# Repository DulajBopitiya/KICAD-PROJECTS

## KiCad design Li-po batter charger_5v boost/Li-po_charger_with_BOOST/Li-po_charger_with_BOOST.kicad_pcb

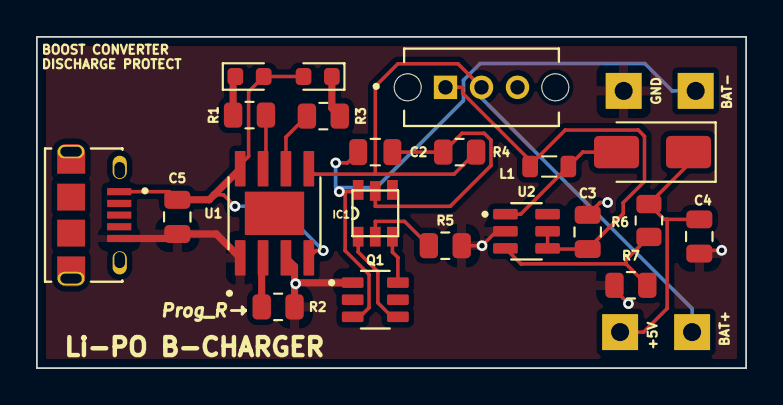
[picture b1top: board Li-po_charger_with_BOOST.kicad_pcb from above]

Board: 2 copper layers, 39.4 x 18.4 mm, 25 parts (0 on the bottom side), 17 nets.

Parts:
C2: 0.1u; C_0805_2012Metric
C3, C4: 22u; C_0805_2012Metric
C5: 10u; C_0805_2012Metric
D1: RED; LED_0603_1608Metric
D2: GREEN; LED_0603_1608Metric
D3: SS34; D_SMA
H1: BAT+; MountingHole_2.2mm_M2_Pad
H2: BAT-; MountingHole_2.2mm_M2_Pad
H4: GND; MountingHole_2.2mm_M2_Pad
H5: +5V; MountingHole_2.2mm_M2_Pad
IC1: FS312F-G; SOT23-6
J2: 10118194-0001LF; AMPHENOL_10118194-0001LF
L1: 22uH; L_0805_2012Metric
Q1: FS8205; SOT95P280X145-6N
R1, R3, R7: 1K; R_0805_2012Metric
R2, R5: 2K; R_0805_2012Metric
R4: 100; R_0805_2012Metric
R6: 7K5; R_0805_2012Metric
S1: OS102011MS2QN1; SW_OS102011MS2QN1
U1: TP4056; SOP127P600X175-9N
U2: MT3608; SOT95P280X145-6N

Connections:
/BAT: H1.1, R4.2, S1.2, U1.5 (BAT)
/BAT-: C2.1, H2.1, IC1.6 (GND), Q1.3
/VBUS: C5.1, D1.2 (A), D2.2 (A), J2.1, U1.4 (VCC), U1.8 (CE)
GND: C3.2, C4.2, C5.2, H4.1, J2.5, Q1.1, R2.2, R5.2, R7.1, U1.1 (TEMP), U1.3 (GND), U2.2 (GND)
unnamed: D1.1 (K), R1.2
unnamed: D2.1 (K), R3.1
unnamed: D3.2 (A), L1.2, U2.1 (SW)
unnamed: C4.1, D3.1 (K), H5.1, R6.2
unnamed: IC1.2 (CS), R5.1
unnamed: IC1.3 (OC), Q1.6
unnamed: IC1.1 (OD), Q1.4
unnamed: C2.2, IC1.5 (VCC), R4.1
unnamed: R2.1, U1.2 (PROG)
unnamed: R1.1, U1.7 (~CHRG)
unnamed: R3.2, U1.6 (~STDBY)
unnamed: C3.1, L1.1, S1.1, U2.4 (EN), U2.5 (IN)
unnamed: R6.1, R7.2, U2.3 (FB)

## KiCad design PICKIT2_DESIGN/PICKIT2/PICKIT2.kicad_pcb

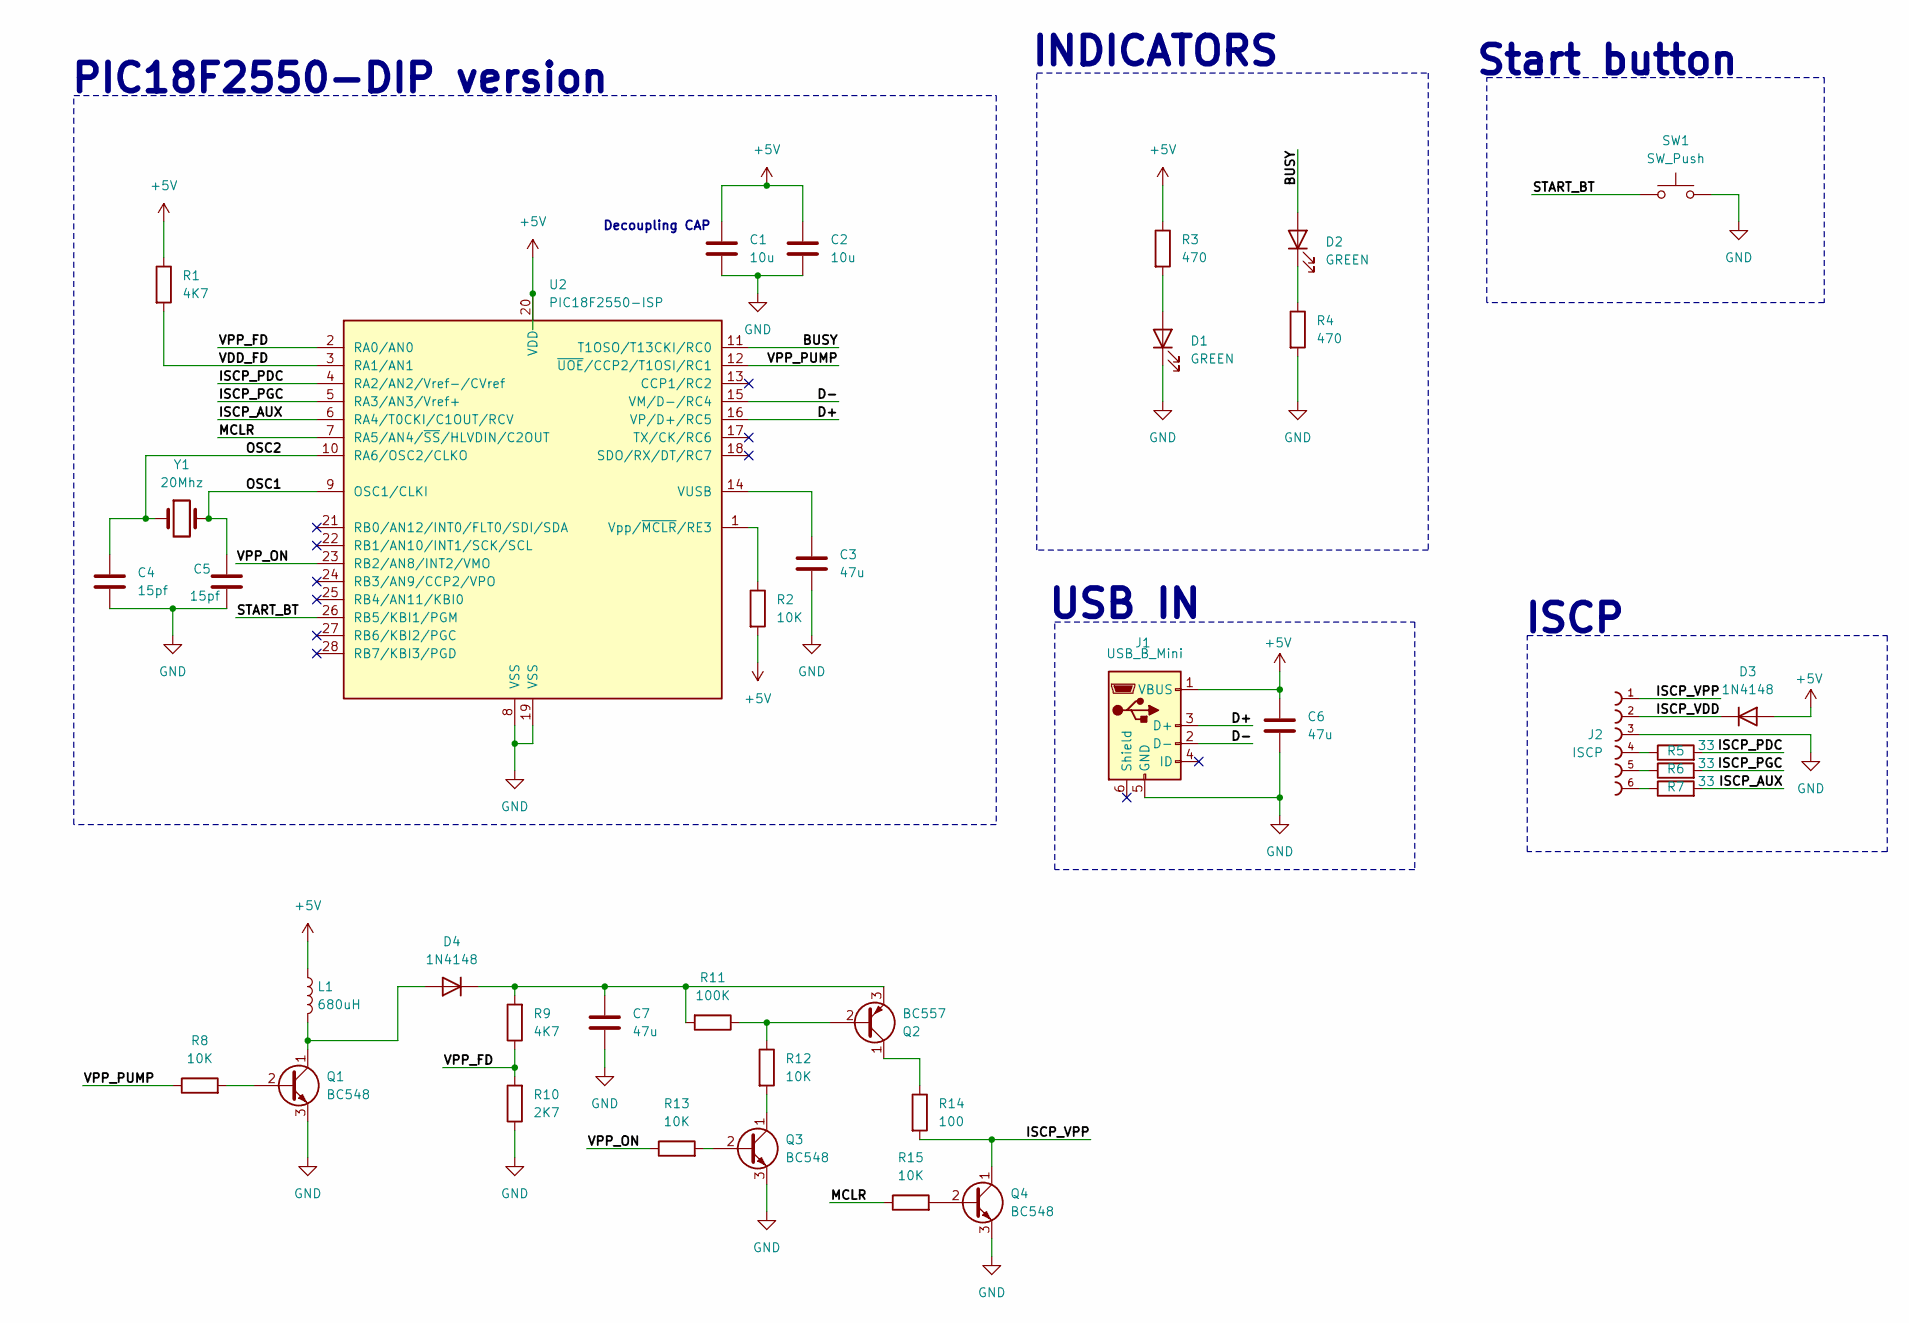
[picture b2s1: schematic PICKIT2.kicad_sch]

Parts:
C1, C2: 10u; C_0805_2012Metric
C3, C6, C7: 47u; C_0805_2012Metric
C4, C5: 15pf; C_0805_2012Metric
D1, D2: GREEN; LED_0805_2012Metric
D3, D4: 1N4148; D_5W_P12.70mm_Horizontal
J1: USB_B_Mini; USB_Micro-B_Molex-105017-0001
J2: ISCP; 62000611121
L1: 680uH; L_Axial_L5.0mm_D3.6mm_P10.00mm_Horizontal_Murata_BL01RN1A2A2
Q1, Q3, Q4: BC548; TO-92_Inline
Q2: BC557; TO-92_Inline
R1, R9: 4K7; R_0805_2012Metric
R2, R8, R12, R13, R15: 10K; R_0805_2012Metric
R3, R4: 470; R_0805_2012Metric
R5, R6, R7: 33; R_0805_2012Metric
R10: 2K7; R_0805_2012Metric
R11: 100K; R_0805_2012Metric
R14: 100; R_0805_2012Metric
SW1: SW_Push; SW_Push_1P1T_XKB_TS-1187A
U2: PIC18F2550-ISP; DIP-28_W7.62mm
Y1: 20Mhz; Crystal_HC51-U_Vertical

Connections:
+5V: C1.1, C2.1, C6.1, D3.2 (A), J1.1 (VBUS), L1.1, R1.1, R2.2, R3.1, U2.20 (VDD)
/BUSY: D2.2 (A), U2.11 (T1OSO/T13CKI/RC0)
/D+: J1.3 (D+), U2.16 (VP/D+/RC5)
/D-: J1.2 (D-), U2.15 (VM/D-/RC4)
/ISCP_AUX: R7.2, U2.6 (RA4/T0CKI/C1OUT/RCV)
/ISCP_PDC: R5.2, U2.4 (RA2/AN2/Vref-/CVref)
/ISCP_PGC: R6.2, U2.5 (RA3/AN3/Vref+)
/ISCP_VDD: D3.1 (K), J2.2
/ISCP_VPP: J2.1, Q4.1 (C), R14.2
/MCLR: R15.1, U2.7 (RA5/AN4/~SS/HLVDIN/C2OUT)
/OSC1: C5.1, U2.9 (OSC1/CLKI), Y1.2
/OSC2: C4.1, U2.10 (RA6/OSC2/CLKO), Y1.1
/START_BT: SW1.1, U2.26 (RB5/KBI1/PGM)
/VDD_FD: R1.2, U2.3 (RA1/AN1)
/VPP_FD: R9.1, R10.2, U2.2 (RA0/AN0)
/VPP_ON: R13.1, U2.23 (RB2/AN8/INT2/VMO)
/VPP_PUMP: R8.1, U2.12 (~UOE/CCP2/T1OSI/RC1)
GND: C1.2, C2.2, C3.2, C4.2, C5.2, C6.2, C7.2, D1.1 (K), J1.5 (GND), J2.3, Q1.3 (E), Q3.3 (E), Q4.3 (E), R4.2, R10.1, SW1.2, U2.8 (VSS), U2.19 (VSS)
unnamed: D1.2 (A), R3.2
unnamed: D2.1 (K), R4.1
unnamed: D4.2 (A), L1.2, Q1.1 (C)
unnamed: C7.1, D4.1 (K), Q2.3 (E), R9.2, R11.2
unnamed: J2.4, R5.1
unnamed: J2.5, R6.1
unnamed: J2.6, R7.1
unnamed: Q1.2 (B), R8.2
unnamed: Q2.2 (B), R11.1, R12.1
unnamed: Q2.1 (C), R14.1
unnamed: Q3.2 (B), R13.2
unnamed: Q3.1 (C), R12.2
unnamed: Q4.2 (B), R15.2
unnamed: C3.1, U2.14 (VUSB)
unnamed: R2.1, U2.1 (Vpp/~MCLR/RE3)

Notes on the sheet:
USB IN
Decoupling CAP
ISCP
INDICATORS
PIC18F2550-DIP version
Start button

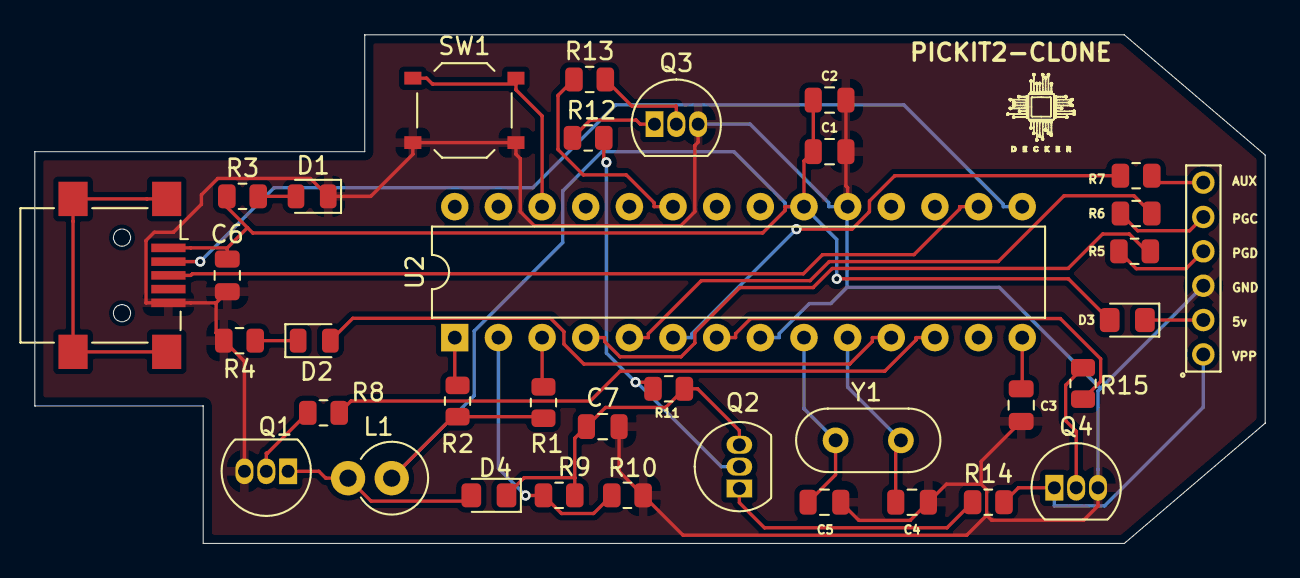
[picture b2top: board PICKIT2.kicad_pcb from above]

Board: 2 copper layers, 71.6 x 29.6 mm, 36 parts (0 on the bottom side), 33 nets.

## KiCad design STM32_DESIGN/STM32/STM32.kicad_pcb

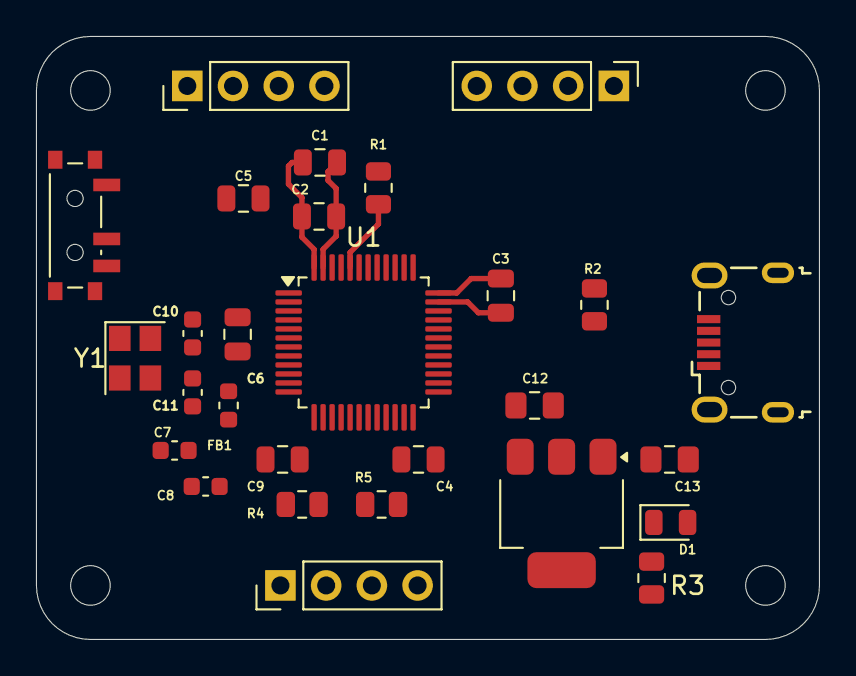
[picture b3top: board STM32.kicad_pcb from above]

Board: 2 copper layers, 43.5 x 33.5 mm, 32 parts (0 on the bottom side), 18 nets.

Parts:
C1, C2, C3, C4, C9: 100n; C_0805_2012Metric
C5: 10u; C_0805_2012Metric
C6: 10n; C_0805_2012Metric
C7, C8: 1u; C_0603_1608Metric
C10, C11: 10p; C_0603_1608Metric
C12, C13: 22uf; C_0805_2012Metric_Pad1.18x1.45mm_HandSolder
D1: RED; LED_0805_2012Metric
FB1: 120R; L_0603_1608Metric
H1, H2, H3, H4: MountingHole; MountingHole_2.2mm_M2
J1: USB_B_Micro; USB_Micro-B_Wuerth_629105150521
J2, J3, J4: Conn_01x04_Pin; PinHeader_1x04_P2.54mm_Vertical
R1: 10K; R_0805_2012Metric
R2, R3, R5: 1K5; R_0805_2012Metric
R4: 1k5; R_0805_2012Metric
SW1: SW_SPDT; SW_SPDT_PCM12
U1: STM32F103C8T6; LQFP-48_7x7mm_P0.5mm
U2: AMS1117-3.3; SOT-223-3_TabPin2
Y1: 16Mhz; Crystal_SMD_3225-4Pin_3.2x2.5mm

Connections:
+3.3V: C1.1, C2.1, C3.1, C4.1, C5.1, C8.1, C13.1, D1.2 (A), FB1.2, J2.4, J3.1, J4.1, R2.2, R4.1, R5.1, SW1.3 (C), U1.1 (VBAT), U1.24 (VDD), U1.36 (VDD), U1.48 (VDD), U2.2 (VO)
+3.3VA: C6.1, C7.1, FB1.1, U1.9 (VDDA)
/BOOTO: R1.2, U1.44 (BOOT0)
/HSE_IN: C10.1, U1.5 (PD0), Y1.1
/HSE_OUT: C11.1, U1.6 (PD1), Y1.3
/NRST: C9.1, U1.7 (NRST)
/SWCLK: J2.2, U1.37 (PA14)
/SWDIO: J2.3, U1.34 (PA13)
/SW_BOOTO: R1.1, SW1.2 (B)
/USART1_RX: J3.3, U1.43 (PB7)
/USART1_TX: J3.2, U1.42 (PB6)
/USB_D+: J1.3 (D+), R2.1, U1.33 (PA12)
/USB_D-: J1.2 (D-), U1.32 (PA11)
/i2c2_SCL: J4.2, R4.2, U1.21 (PB10)
/i2c2_SDA: J4.3, R5.2, U1.22 (PB11)
GND: C1.2, C2.2, C3.2, C4.2, C5.2, C6.2, C7.2, C8.2, C9.2, C10.2, C11.2, C12.2, C13.2, J1.5 (GND), J2.1, J3.4, J4.4, R3.1, SW1.1 (A), U1.8 (VSSA), U1.23 (VSS), U1.35 (VSS), U1.47 (VSS), U2.1 (GND), Y1.2, Y1.4
unnamed: D1.1 (K), R3.2
VBUS: C12.1, J1.1 (VBUS), U2.3 (VI)
